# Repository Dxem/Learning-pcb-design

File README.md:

# Learning-pcb-design

Im learning pcb design - so everything i do in this repo is open source and you are free to use this designs

Dziennik nauki projektowania elektroniki — od schematu, przez layout PCB, po zamówienie, montaż i uruchomienie. Repo służy jednocześnie jako log postępu i portfolio kolejnych projektów.

## Struktura repozytorium

```
Learning-pcb-design/
├── README.md                          ← ten plik
├── LICENSE                            ← Apache 2.0
├── docs/
│   ├── components-reference.md        ← baza wiedzy o komponentach projektu 01 (symbole, footprinty, dostępność do montażu PCBA)
│   └── project-log-template.md        ← szablon wpisu do logu postępu (kopiuj do każdego projektu)
└── projects/
    ├── 01-stm32-mini-devboard/        ← mini płytka dev STM32F411 — też reużywalny "carrier" MCU do testowania modułów 02-05
    ├── 02-nrf24-radio-module/         ← moduł: radio 2.4GHz (nRF24L01+), antena, SPI
    ├── 03-audio-adc-frontend/         ← moduł: wejście audio (jack → PCM1808 → I2S)
    ├── 04-audio-dac-backend/          ← moduł: wyjście audio (I2S → PCM5102A → wzmacniacz → jack)
    ├── 05-power-module/               ← moduł: bateria LiPo, ładowanie USB-C, ochrona, LDO
    └── 06-piano-audio-integration/    ← integracja modułów 02-05 w finalne płytki TX/RX
```

Każdy projekt ma tę samą strukturę wewnętrzną: `README.md` (cel, zakres, BOM, log postępu), `docs/` (plan/architektura, notatki), `hardware/kicad*/` (pliki KiCad). Dzięki temu repo skaluje się bez przebudowy, a każdy projekt jest samodzielnie czytelny — także dla kogoś oglądającego to jako portfolio.

**Wzorzec "carrier + moduły":** od projektu 02 każdy nowy, mniejszy moduł (radio, audio-in, audio-out, zasilanie) projektowany jest bez własnego MCU — podpina się przewodami do płytki z projektu 01, która pełni rolę wielokrotnego użytku platformy testowej. To pozwala uczyć się każdej dziedziny (RF, audio, power) osobno, zweryfikować ją oscyloskopem w izolacji, i dopiero potem łączyć sprawdzone bloki w finalną, złożoną płytkę (projekt integracyjny, np. 06).

Uwaga: `docs/components-reference.md` w repo głównym dotyczy konkretnie projektu 01 — każdy kolejny projekt trzyma własną dokumentację komponentów w swoim `README.md`/`docs/`, żeby nie mieszać BOM-ów różnych projektów w jednym pliku.

## Konwencja logu postępu

Każdy projekt ma w swoim `README.md` sekcję **Log postępu** — krótkie, datowane wpisy (co zrobiłem, co nie zadziałało, czego się nauczyłem). To najcenniejsza część repo z punktu widzenia nauki i najbardziej wiarygodna dla kogoś czytającego portfolio — pokazuje proces, nie tylko efekt końcowy.

## Status projektów

| Projekt | Status | Opis |
|---|---|---|
| [01-stm32-mini-devboard](projects/01-stm32-mini-devboard/) | 🟢 Gotowe -  dobór komponentów zakończony, schemat - 🟢, pcb layout - 🟢  | Minimalna płytka dev ze STM32F411, USB-C, SWD; też carrier testowy dla modułów 02-05 Start: 24.08.2026 Koniec 03.09.2026 |
| [02-nrf24-radio-module](projects/02-nrf24-radio-module/) | 🟡 w toku — plan gotowy, schemat do zrobienia | Moduł radiowy nRF24L01+ (bare chip), własna antena, test punkty na SPI Start: 28.09.2026|
| [03-audio-adc-frontend](projects/03-audio-adc-frontend/) | ⚪ czeka — plan gotowy, schemat do zrobienia | Wejście audio: jack 3.5mm → PCM1808 (ADC) → I2S |
| [04-audio-dac-backend](projects/04-audio-dac-backend/) | ⚪ czeka — plan gotowy, schemat do zrobienia | Wyjście audio: I2S → PCM5102A (DAC) → NS4160 (wzmacniacz) → jack 3.5mm |
| [05-power-module](projects/05-power-module/) | ⚪ czeka — plan gotowy, schemat do zrobienia | Bateria LiPo + ładowanie USB-C + ochrona (DW01A) + LDO 3.3V |
| [06-piano-audio-integration](projects/06-piano-audio-integration/) | ⚪ czeka — architektura i BOM gotowe, czeka na moduły 02-05 | Integracja sprawdzonych modułów w finalne płytki TX/RX do cichej gry na pianinie w nocy |

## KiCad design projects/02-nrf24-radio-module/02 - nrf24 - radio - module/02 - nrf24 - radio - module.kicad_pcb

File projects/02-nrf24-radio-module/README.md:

# 02 — Moduł radiowy nRF24L01+ (samodzielna sesja nauki RF)

Status: 🟡 w toku — plan gotowy, schemat do zrobienia

Pierwszy z czterech mniejszych modułów, na które rozbiłem [projekt integracyjny 06](../06-piano-audio-integration/) (bezprzewodowy link audio TX/RX). Zamiast projektować od razu całą, złożoną płytkę TX/RX, uczysz się każdej dziedziny osobno na małej, testowalnej płytce. Ten moduł: **RF — dopasowanie anteny i cyfrowa komunikacja SPI z radiem.**

## Zakres

- **nRF24L01+** — bare chip QFN20, własny layout anteny wg referencji Nordica (bez modułu z gotową anteną — to jest właśnie ćwiczenie RF)
- Złącze/pady wyprowadzające SPI (SCK, MOSI, MISO, CSN, CE, IRQ) + 3V3 + GND — **do podpięcia przewodami do płytki z projektu 01** (Twój mini dev board STM32F411) zamiast projektowania osobnego MCU na tej płytce. Reużywasz już zbudowany sprzęt zamiast duplikować MCU w każdym module.
- Bez własnego zasilacza — 3.3V bierzesz z płytki STM32 (project 01 ma już regulator na pokładzie); dodaj tylko lokalny kondensator blokujący blisko radia (nRF24 jest czuły na szum na linii zasilania).

## Test punkty pod oscyloskop/analizator stanów logicznych

Dodaj wyprowadzone pady testowe (małe pady/via, opisane na sitodruku) na:

- **SCK, MOSI, MISO, CSN, CE, IRQ** — wszystkie sygnały cyfrowe SPI, idealne do oscyloskopu/analizatora logicznego. Zobaczysz realny protokół komunikacji z radiem, timing transakcji SPI, kiedy CE się aktywuje przy nadawaniu itd.
- **GPIO testowy z MCU, przełączany na początku/końcu wysyłki pakietu** — to jest Twój sposób na **zmierzenie realnego opóźnienia** transmisji: przełącz jeden GPIO na TX w momencie wysyłki, drugi GPIO na RX w momencie odbioru, i zmierz różnicę czasu na dwukanałowym oscyloskopie. To najważniejszy pomiar w całym projekcie 06 (uzasadnia, czy w ogóle warto grać na tym w czasie rzeczywistym).

**Ważne zastrzeżenie:** samego sygnału radiowego 2.4GHz **nie zobaczysz sensownie na typowym hobbystycznym oscyloskopie** — standardowa sonda pasywna (nawet 10x) ma pojemność rzędu 10-15pF, która przy 2.4GHz realnie rozstraja dopasowanie anteny i daje mylący odczyt, a większość hobbystycznych oscyloskopów ma pasmo 50-100MHz, dalece za mało na 2.4GHz. Do weryfikacji samego RF potrzebny byłby analizator widma albo sonda aktywna wysokiej impedancji. To nie problem — to, co realnie chcesz zobaczyć (protokół SPI i opóźnienie end-to-end), jest w pełni dostępne na zwykłym oscyloskopie.

## Plan budowy i testu

1. Zbuduj **dwie sztuki** tej samej płytki (rola TX/RX ustalana firmware'em, nie sprzętem) — potrzebujesz dwóch egzemplarzy do przetestowania linku. Jeśli zamówiłeś ≥2 sztuki płytki z projektu 01 w PCBA, masz już dwa carriery MCU do tego celu.
2. Podłącz oba moduły do dwóch płytek STM32 z projektu 01.
3. Firmware: najprostszy możliwy — jeden wysyła licznik/wzorzec testowy, drugi odbiera i zapala LED przy poprawnym odbiorze.
4. Zmierz opóźnienie GPIO-to-GPIO na oscyloskopie (patrz wyżej).
5. Dopiero po potwierdzeniu działającego linku i sensownego opóźnienia — przechodzisz do modułu 03/04 (audio).

## BOM

| Komponent | Część | LCSC/JLCPCB | Uwagi |
|---|---|---|---|
| Radio | NRF24L01P-R | `C8791` | Bare chip QFN20 |
| Kondensator blokujący | 100nF + większy elektrolityczny/tantalowy blisko radia | Basic Parts | Zasilanie radia musi być czyste |
| Pady testowe | np. `TestPoint:TestPoint_Pad_D1.0mm` w KiCad | — | Na każdej linii SPI + CE + IRQ |

## Struktura folderu

```
02-nrf24-radio-module/
├── README.md               ← pełny plan modułu (ten plik zawiera wszystko: zakres, BOM, test punkty)
├── docs/                   ← na przyszłość: datasheety, notatki z bring-up, zdjęcia
├── hardware/
|    └── kicad/
└── simulation/
```

## Log postępu

### 2026-09-28 — Rozpoczęcie prac

**Co zrobiłem:**
-  Przeczytałem datasheet modułu nrf24l01p 
- zdecydowałem się nie wykorzystywać nowszego modułu nrf54l01 ponieważ wymaga on obudowy qfn 48 co bezpośrednio wpływa na rozrośnięcie się płytki do mniej więcej wielkości devboarda. Moduł radiowy ma mieć postać shielda a do nauki nowszego modułu poświęcę oddzielny projekt

**Czego się nauczyłem:**
- Standardowy oscyloskop hobbystyczny nie nadaje się do bezpośredniego podglądu sygnału 2.4GHz (pojemność sondy rozstraja antenę, pasmo za wąskie) — ale cyfrowa strona (SPI, timing pakietów) jest w pełni dostępna i to ona faktycznie odpowiada na pytanie "czy to działa wystarczająco szybko"
- romiar obudów komponentów w sekcji dopasowującej wyjście do antenowego 50 ohm ma znaczenie ze względu na efekty pasożytnicze

**Następny krok:**
- Schemat w KiCad: nRF24L01+ + referencyjna antena + złącze do carriera STM32
- zmiana dotychczasowo dobranych komponentó na mniejszy footprint w miejscach gdzie ma to szczególne znaczenie.

### 2026-10-16 — Ogólny schemat

**Co zrobiłem:**
-  Wyprowadziłem piny do fizycznej weryfikacji sygnałów 
- rozpoczęto budowę modelu do dopasowania anteny - wzorując się na application notes Nordic semiconductors, jednak w mojej aplikacji może się okazać że wartości konkretnych elementów mogą się różnić - z tego względu warto zrobić symulację

**Czego się nauczyłem:**
- Pomimo faktu, że nordic semiconductors sprawdziło konkretne dopasowanie do anteny - jest ono sprawdzone jedynie dla ich konkretnego layoutu - dla customowych rozwiązań należy stosować customowe dopasowania.
- Wykorzystywanie biblioteki scikit-rf - rozpocząłem naukę i postawiłem pierwsze kroki

**Następny krok:**
- zrealizować symulację
- dobrać komponenty do wyników symulacji
  
### 2026-10-18 — Początek dopasowania anteny

**Co zrobiłem:**
-  Wybrałem gotowe rozwiązanie anteny na 2.4 GHz zoptymalizowaną przez Texas Instruments 2.4-GHz Inverted F Antenna (Rev. D)
-  Dobrałem Oscylator kwarcowy oraz kondensatory obciążeniowe

**Czego się nauczyłem:**
- niektóre rozwiązania takie jak na przykład konkretny kształt anteny są publicznie i powszechnie dostępne - są zoptymalizowane i udokumentowane do takich właśnie projektów jak ten
- kondensatory w okolicach rezonatorów kwarcowych powinny mieć dielektryk taki jak NP0 lub C0G - nie zmieniać swojej pojemności pod wpływem różnic temperatury

**Następny krok:**
- zrealizować symulację
- dobrać komponenty do wyników symulacji
- pcb layout

### 2026-10-19 — Symulacje do dopasowania anteny

**Co zrobiłem:**
-  Wykonano wstępną analizę symulacyjną dla układu proponowanego przez Nordic Semiconductors w nocie aplikacyjnej
-  Oceniono tolerancje na efekty pasożytnicze dla układu zaproponowanego przez Nordic
-  Analiza Smith Chart i SWR

**Czego się nauczyłem:**
- Nota aplikacyjna proponuje 15+j88Ω jednak z symulacji wynika 19 + j30 Ω, czyli brakuje 1.9nH na każdy pin - różnice mogą wynikać zarówno z obudowy jak i samych długości ścieżek
- Budżet na dodatkowe ścieżki przy ANT1/ANT2 to tylko ok. 0,25 nH, czyli ułamek milimetra. Dopasowanie jest ciasne, bo część rzeczywista impedancji to ok. 10–20 Ω
- Antyrezonans C3–C4 w węźle VDD_PA. Jeśli gałąź C3 ma więcej niż ok. 0,5 nH, węzeł przestaje być masą dla w.cz. i balun przestaje działać. (Prawdziwy kondensator to tak naprawdę cewka z kondensatorem w szeregu)

**Następny krok:**
- pcb layout
- rozbudować symulację po layoucie - teraz już wiem czego się teoretycznie spodziewać
- dobrać komponenty do wyników symulacji

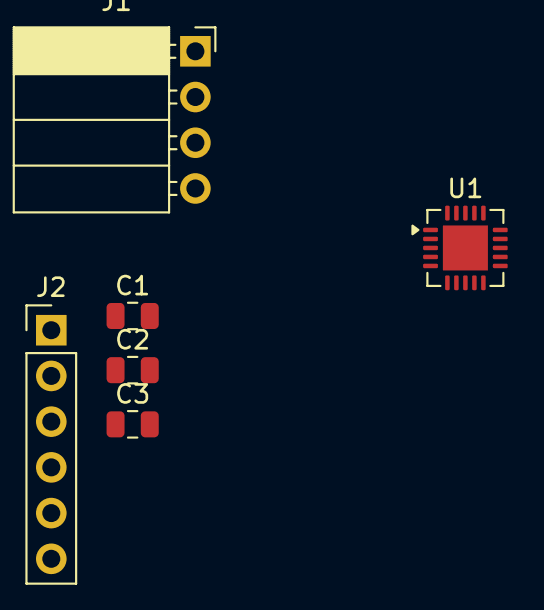
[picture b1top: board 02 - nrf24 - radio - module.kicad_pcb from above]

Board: 2 copper layers, 6 parts (0 on the bottom side), 9 nets, no tracks yet.

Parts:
C1: 10n; C_0805_2012Metric
C2: 1n; C_0805_2012Metric
C3: 33n; C_0805_2012Metric
J1: SPI CONNECTOR; PinSocket_1x04_P2.54mm_Horizontal
J2: MONITOR_Header; PinHeader_1x06_P2.54mm_Vertical
U1: nRF24L01P; QFN-20-1EP_4x4mm_P0.5mm_EP2.5x2.5mm

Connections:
CE: J2.5, U1.1 (CE)
CSN: J1.4, J2.4, U1.2 (CSN)
GND: C1.2, C2.2, C3.2
IRQ: J2.6, U1.6 (IRQ)
MISO: J1.3, J2.3, U1.5 (MISO)
MOSI: J1.2, J2.2, U1.4 (MOSI)
unnamed: C3.1, U1.19 (DVDD)
SCK: J1.1, J2.1, U1.3 (SCK)
VDD: C1.1, C2.1, U1.7 (VDD), U1.15 (VDD), U1.18 (VDD)

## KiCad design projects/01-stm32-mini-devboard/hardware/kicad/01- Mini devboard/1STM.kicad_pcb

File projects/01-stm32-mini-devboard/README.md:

# 01 — Mini płytka rozwojowa STM32F412

Status: 🟢 Wykonany layout PCB gotowe do zamówienia (etap: przygotowanie do schematu)

Pierwszy projekt w tym repo. Cel: przejść cały proces projektowania elektroniki — schemat → PCB → produkcja → montaż → uruchomienie — na małej, tanio produkowalnej płytce.

**Dodatkowa rola od projektu 02:** ta płytka służy też jako wielokrotnego użytku "carrier" MCU do testowania mniejszych modułów ([02-nrf24-radio-module](../02-nrf24-radio-module/), [03-audio-adc-frontend](../03-audio-adc-frontend/), [04-audio-dac-backend](../04-audio-dac-backend/)) - podpinasz je przewodami do jej złączy GPIO/SPI/I2S zamiast projektować osobny MCU na każdej mniejszej płytce. Do zamówienia przynajmniej 2 szt do testów linka radiowego.

## Zakres (v1)

- Zasilanie z USB-C (5V → 3.3V przez LDO)
- MCU: STM32F412CEU6 (UFQFPN-48)
- Programowanie/debug: złącze SWD jako prosty rządek 2.54mm (4-5 pin), pod montaż PCBA zamiast box headera
- BOOT0 na pull-downie (bez przełącznika na v1)
- Montaż: docelowo **zamawiany PCBA w JLCPCB** (nie ręczne lutowanie) — patrz baza komponentów po numery LCSC
- 1 LED użytkownika + 1 LED zasilania
- Przycisk RESET + przycisk User
- Kryształ HSE
- Wyprowadzone GPIO na goldpinach

Pełny opis etapów pracy, checklisty i zasady projektowe: patrz [`docs/plan-projektu.md`](docs/plan-projektu.md) oraz [`../../docs/components-reference.md`](../../docs/components-reference.md) w repo głównym.

## Dokumentacja komponentów

Zebrana w [`../../docs/components-reference.md`](../../docs/components-reference.md) — datasheety, źródła symboli/footprintów, decyzje projektowe dla każdego komponentu.

## Struktura folderu

```
01-stm32-mini-devboard/
├── README.md               ← ten plik
├── docs/
│   └── plan-projektu.md    ← pełny plan: etapy, zasady projektowe, checklisty
├── hardware/               ← projekt płytki
│   └── kicad/
│       ├── 1STM.kicad_pro
│       ├── 1STM.kicad_sch
│       ├── 1STM.kicad_pcb
│       └── 1STM.kicad_prl
├── testing/                ← testowanie fizycznych egzemplaży
└── simulation/             ← teoretyczne przygotowanie pd fizyczne testowanie
```

## Log postępu

### 2026-08-24 — start projektu, dobór komponentów

**Co zrobiłem:**
    - Ustaliłem zakres v1 płytki (patrz wyżej)
    - Zebrałem dokumentację i potwierdziłem dostępność symboli/footprintów dla: STM32F412CEU6, złącze USB-C
    - Założyłem strukturę repozytorium
    - Stworzyłem sekcję zasilania do mcu 

**Czego się nauczyłem:**
- Dla większości popularnych komponentów nie trzeba rysować footprintów od zera — warto najpierw sprawdzić bibliotekę wbudowaną KiCad, potem SnapMagic/Ultra Librarian, dopiero na końcu rysować ręcznie
- USB-C wymaga rezystorów 5.1kΩ pull-down na CC1/CC2, inaczej port może nie podać zasilania

**Następny krok:**
- Zweryfikować pobrane/wbudowane symbole i footprinty 1:1 z datasheetami
- Zbudować schemat w KiCad (zasilanie → MCU → peryferia → złącza)

### 2026-08-25 —  Schemat p. 1 Sekcja zasilania

**Co zrobiłem:**
    - ciąg dalszy zbierania dokumentacji ze strony jlcpcb i doboru komponentów 
    - nauka pracy z dokumentacją - wyszukiwania sekcji w datasheecie któe właściwie zaprezentują rozwiązanie możliwe do zaimplementowania w aplikacji
    - Sekcja zasilania płytki - dokończyłem
**Co nie zadziałało / problemy:**
    - Nie wykorzystywałem jeszcze na tamtym etapie net names i global labels - bardzo przydatne narzędzia 
**Czego się nauczyłem:**
    - Organizacja schematu w sekcje i wykorzystanie kondensatoró decapujących bardzo
**Następny krok:**
    - Połączenie z MCU

### 2026-08-26 — Schemat p. 2 MCU

**Co zrobiłem:**
    - Zestaw połaczeń z MCU z sekcji zasilania
    - Wybór komponentów do peryferiów zgodnych z planem projektu
    - Poznawanie alternate functions
**Co nie zadziałało / problemy:**
    -I2C i I2S to dwie inne rzeczy
**Czego się nauczyłem:**
    - Ten sam moduł może realizować dwie funkcje jednocześnie więc jeśli mają ze sobą rozmawiać to lepiej aby były z dwóch innych modułów
    - I2C i I2S to dwie inne rzeczy
**Następny krok:**
    - dokończyć schemat zacząć z pcb

### 2026-08-27 — Schemat p. 3 Peryferia

**Co zrobiłem:**
    - Sekcja peryferiów
    - Optymalizacja netów
    - Poprawki wizualne schematu
    - Dodane diody LED
    - Przyciski     
**Co nie zadziałało / problemy:**
    - Lepiej zmienić diodę na inny kolor niż niebieski niż nie zastosować żadnego rezystora ograniczającego prąd mimo że napięcie odpowiada napięciu pracy diody
**Czego się nauczyłem:**
    - Lepiej zmienić diodę na inny kolor niż niebieski niż nie zastosować żadnego rezystora ograniczającego prąd mimo że napięcie odpowiada napięciu pracy diody
**Następny krok:**
    - PCB Layout

### 2026-09-02 — PCB Layout p. 1 Initial Layout

**Co zrobiłem:**
    - initial PCB layout
    - Dodany kryształ HSE
    - Dobór kondensatorów do kryształu
**Co nie zadziałało / problemy:**
    - Pierwsze próby posegregowania komponentów - wymaga doświadczenia aby właściwie podzielić na sekcje lub parę iteracji
**Czego się nauczyłem:**
    - Kryształ może mieć różne Load capacitance w zależności od tego co się zamawia - należy zwrócić uwagę
    - dobór kondensatoró do kryształu
**Następny krok:**
    - dokończyć PCB layout

### 2026-09-03 — PCB Layout p. 2 Layout opcja A

**Co zrobiłem:**
    - pierwsza propozycja pcb layout
    - znikome wykorzystanie warstwy B.Cu - głównie skłąda się z ground plane
**Co nie zadziałało / problemy:**
    - Powinienem lepiej przemyśleć kolejność wykonywanie routingu - do wdrożenia w nastepnej wersji
**Czego się nauczyłem:**
    - Tworzenie obrysu PCB
    - Wylewanie Ground plane
    - Layout ścieżek w usb - c
**Następny krok:**
    - Powtórzyć drugi raz routing z wiedzą którą nabyłem przy tej próbie - zobaczymy co się da poprawić
### 2026-09-29 — Update

**UPDATE:**
    - Routing nie będzie jeszcze raz realizowany - rezultat jest wystarczający, a optymalizację konstrukcji można wykonywać w nieskończoność
    - Projekt oprócz schematów hardwareu będzie zawierał również symulację oraz realne pomiary do porównania z teorią

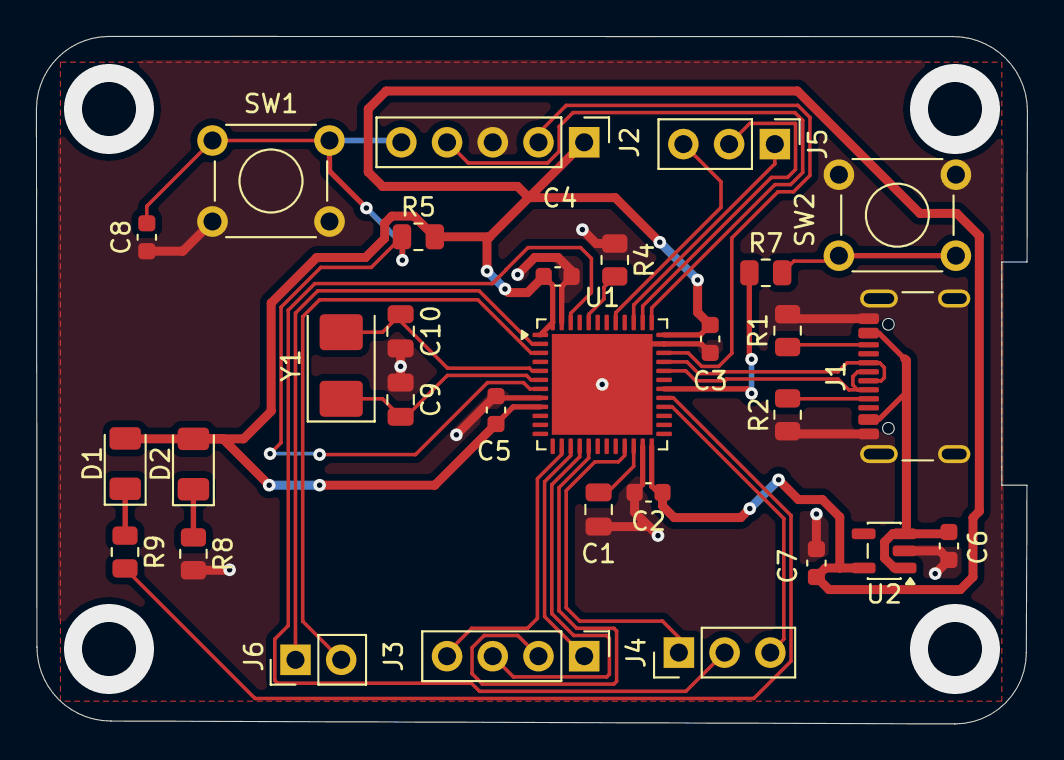
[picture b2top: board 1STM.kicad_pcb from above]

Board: 2 copper layers, 55.1 x 38.2 mm, 30 parts (0 on the bottom side), 31 nets.

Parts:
C1: 4u7; C_0805_2012Metric
C2, C3, C4, C5, C8: 100nF; C_0603_1608Metric
C6, C7: 1u; C_0603_1608Metric
C9, C10: 30pF; C_0805_2012Metric
D1: AMBER_LED; LED_1206_3216Metric
D2: RED_LED; LED_1206_3216Metric
J1: USB_C_Receptacle_USB2.0_16P; USB_C_Receptacle_GCT_USB4105-xx-A_16P_TopMnt_Horizontal
J2: SWD 5P; PinHeader_1x05_P2.54mm_Vertical
J3: SPI1; PinHeader_1x04_P2.54mm_Vertical
J4: WE I2S2; PinHeader_1x03_P2.54mm_Vertical
J5: WY I2S3; PinHeader_1x03_P2.54mm_Vertical
J6: GPIO; PinHeader_1x02_P2.54mm_Vertical
R1, R2: 5K1; R_0805_2012Metric
R4, R5: 10K; R_0805_2012Metric
R7: 330; R_0805_2012Metric
R8, R9: 65; R_0805_2012Metric
SW1, SW2: B3F-1002; SW_TH_Tactile_Omron_B3F-100x
U1: STM32F412CEUx; QFN-48-1EP_7x7mm_P0.5mm_EP5.6x5.6mm
U2: AP2112K-3.3TRG1; SOT-23-5
Y1: 8MHz; Crystal_SMD_5032-2Pin_5.0x3.2mm

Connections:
+3.3V: C2.1, C3.1, C4.1, C5.1, C7.2, D1.2 (A), D2.2 (A), J2.1, R5.2, U1.1 (VBAT), U1.9 (VDDA), U1.24 (VDD), U1.36 (VDD), U1.48 (VDD), U2.5 (OUT)
+5V: C6.2, J1.A4 (VBUS), J1.A9 (VBUS), J1.B4 (VBUS), J1.B9 (VBUS), U2.1 (VIN), U2.3 (EN)
/GPIO (CE): J6.2, U1.3 (PC14)
/GPIO (IRQ): J6.1, U1.2 (PC13)
/I2S2_CK: J4.1, U1.21 (PB10)
/I2S2_SD: J4.3, U1.28 (PB15)
/I2S2_WS: J4.2, U1.46 (PB9)
/I2S3_CK: J5.1, U1.39 (PB3)
/I2S3_SD: J5.3, U1.41 (PB5)
/SPI1_NSS: J3.4, U1.14 (PA4)
/SPI1_SCK: J3.1, U1.15 (PA5)
/SWCLK: J2.4, U1.37 (PA14)
/SWDIO: J2.2, U1.34 (PA13)
D+_USB: J1.A6 (D+), J1.B6 (D+), U1.33 (PA12)
D-_USB: J1.A7 (D-), J1.B7 (D-), U1.32 (PA11)
GND: C1.1, C2.2, C3.2, C4.2, C5.2, C6.1, C7.1, C8.1, C9.1, C10.2, J1.A1 (GND), J1.A12 (GND), J1.B1 (GND), J1.B12 (GND), J1.SH (SHIELD), J2.3, R1.2, R2.2, R4.1, R8.2, SW1.2, SW2.2, U1.8 (VSSA), U1.23 (VSS), U1.35 (VSS), U1.47 (VSS), U1.49 (VSS), U2.2 (GND)
I2S3_WS: J5.2, U1.38 (PA15)
NRST: C8.2, J2.5, R5.1, SW1.1, U1.7 (NRST)
unnamed: D1.1 (K), R9.1
unnamed: D2.1 (K), R8.1
unnamed: J1.A5 (CC1), R2.1
unnamed: J1.B5 (CC2), R1.1
unnamed: R7.2, SW2.1
unnamed: R4.2, U1.44 (BOOT0)
unnamed: C1.2, U1.22 (VCAP_1)
OSC_IN: C10.1, U1.5 (PH0), Y1.2
OSC_OUT: C9.2, U1.6 (PH1), Y1.1
SPI1_MISO: J3.3, U1.16 (PA6)
SPI1_MOSI: J3.2, U1.17 (PA7)
USR_LED: R9.2, U1.29 (PA8)
USR_SW: R7.1, U1.30 (PA9)
